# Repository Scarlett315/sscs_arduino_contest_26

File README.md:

Documentation & process can be found [here](https://medium.com/@scarlettchen315/lock-in-box-2-functional-version-dc13c8e9974b).

Includes 3-D printed box, custom PCB, and Arduino code.

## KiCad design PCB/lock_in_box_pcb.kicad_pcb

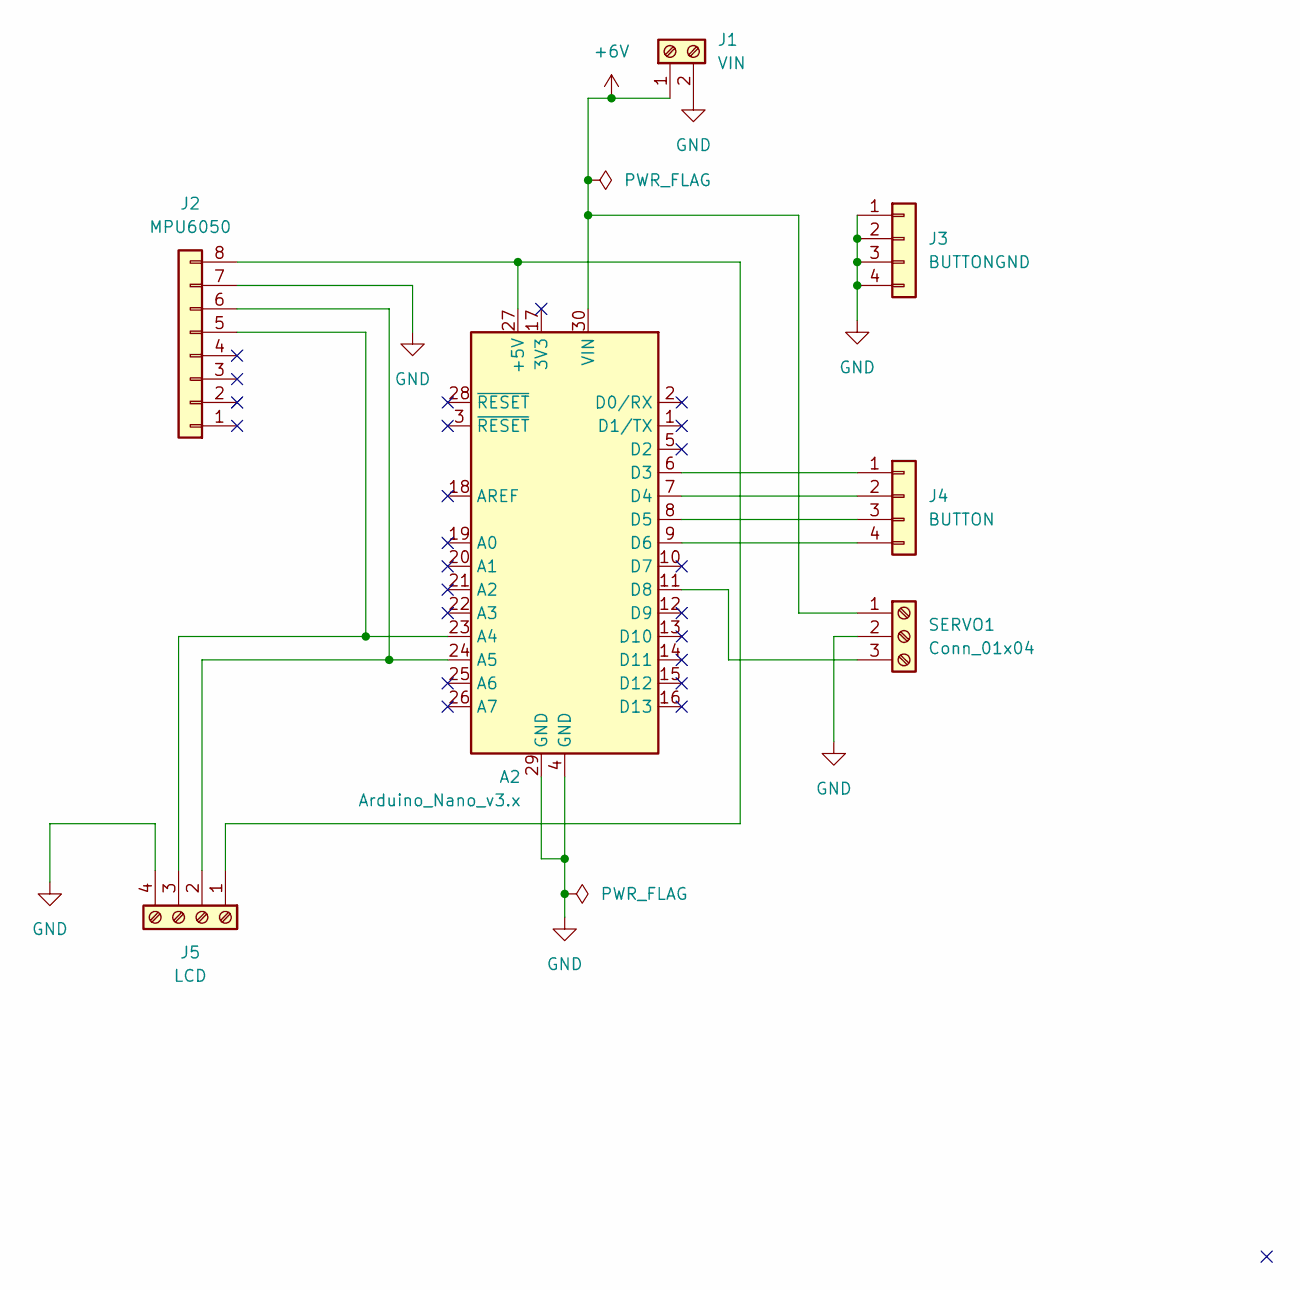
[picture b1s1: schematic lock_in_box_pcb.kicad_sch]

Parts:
A2: Arduino_Nano_v3.x; Arduino_Nano
J1: VIN; PhoenixContact_SPT_1.5_2-H-3.5_1x02_P3.5mm_Horizontal
J2: MPU6050; PinHeader_1x08_P2.54mm_Vertical
J3: BUTTONGND; PinHeader_1x04_P2.54mm_Vertical
J4: BUTTON; PinHeader_1x04_P2.54mm_Vertical
J5: LCD; PinHeader_1x04_P2.54mm_Vertical
SERVO1: Conn_01x04; PinHeader_1x03_P2.54mm_Vertical

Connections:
+6V: A2.30 (VIN), J1.1, SERVO1.1
GND: A2.4 (GND), A2.29 (GND), J1.2, J2.7, J3.1, J3.2, J3.3, J3.4, J5.4, SERVO1.2
unnamed: A2.27 (+5V), J2.8, J5.1
unnamed: A2.23 (A4), J2.5, J5.3
unnamed: A2.24 (A5), J2.6, J5.2
unnamed: A2.6 (D3), J4.1
unnamed: A2.7 (D4), J4.2
unnamed: A2.8 (D5), J4.3
unnamed: A2.9 (D6), J4.4
unnamed: A2.11 (D8), SERVO1.3

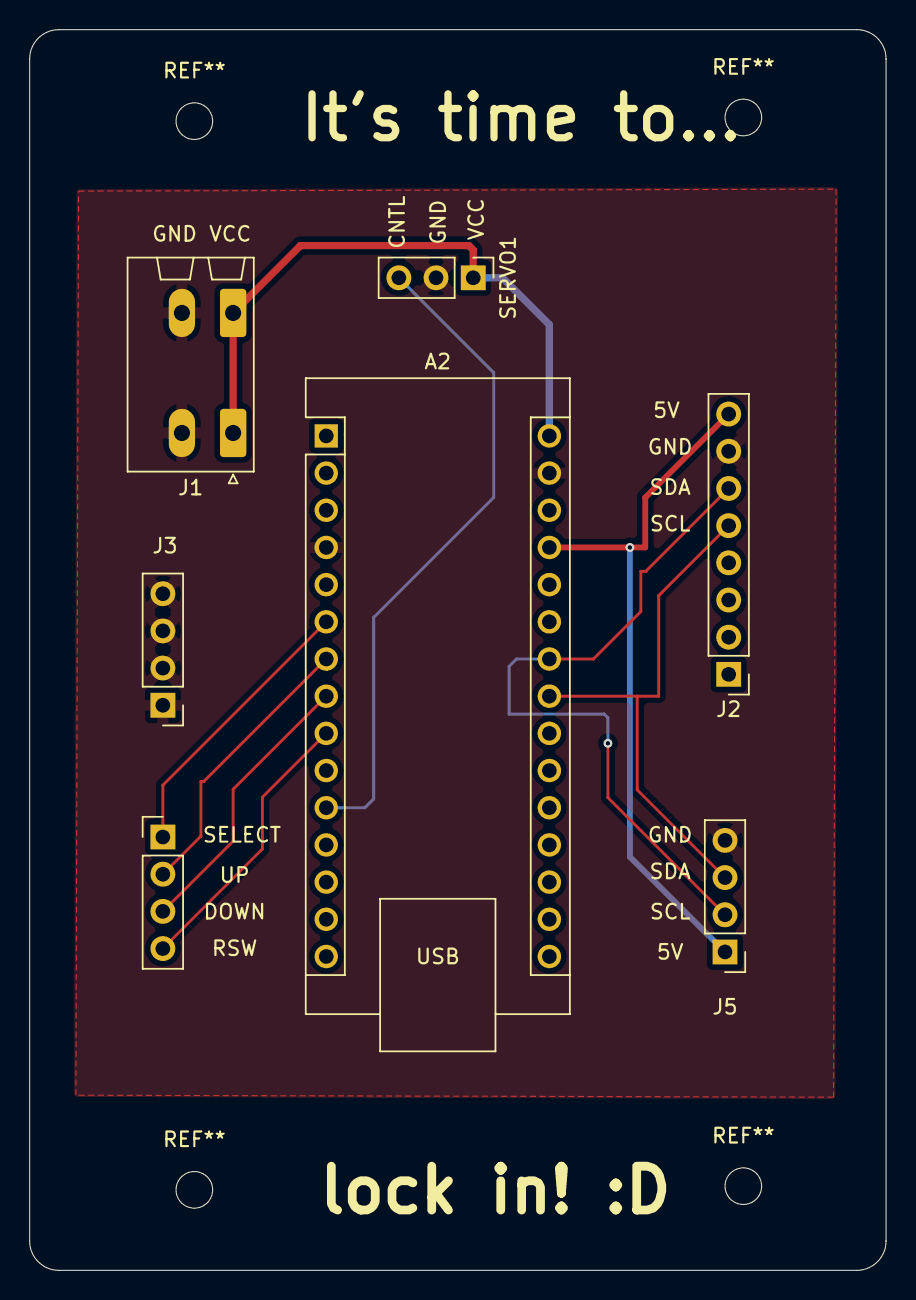
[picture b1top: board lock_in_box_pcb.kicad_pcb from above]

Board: 2 copper layers, 58.5 x 84.8 mm, 7 parts (0 on the bottom side), 10 nets.

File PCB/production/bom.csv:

Designator,Footprint,Quantity,Value,LCSC Part #
A2,Arduino_Nano,1,Arduino_Nano_v3.x,
J1,PhoenixContact_SPT_1.5_2-H-3.5_1x02_P3.5mm_Horizontal,1,VIN,
J2,PinHeader_1x08_P2.54mm_Vertical,1,MPU6050,
J3,PinHeader_1x04_P2.54mm_Vertical,1,BUTTONGND,
J4,PinHeader_1x04_P2.54mm_Vertical,1,BUTTON,
J5,PinHeader_1x04_P2.54mm_Vertical,1,LCD,
SERVO1,PinHeader_1x03_P2.54mm_Vertical,1,Conn_01x04,
